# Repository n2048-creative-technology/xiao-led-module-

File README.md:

# XIAO LED Module

A 44 x 21 mm addressable-LED panel built around a **Seeed Studio XIAO
ESP32-C3**, driving **50 WS2812B-compatible RGB LEDs** (2020 package)
arranged as two 25-LED daisy chains, plus a 4-pin JST-PH connector for
external power/data breakout.

## 3D Renders

| Top side (LED array) | Bottom side (XIAO socket) |
|---|---|
|  |  |

## Schematic

Full-resolution vector version: [`docs/images/schematic.pdf`](docs/images/schematic.pdf)

## PCB Layout

*Copper (F.Cu / B.Cu), silkscreen, and solder mask layers, board outline shown.*

## Board Specs

- **Size:** 44.05 mm x 21.05 mm
- **Layers:** 2 (F.Cu / B.Cu)
- **MCU:** Seeed Studio XIAO ESP32-C3 (socketed, not soldered — see Manufacturing below)
- **LEDs:** 50x WS2812B-compatible addressable RGB LED, 2020 package,
  arranged as two independent 25-LED daisy chains (LEDA / LEDB) driven
  from separate GPIO pins
- **Power/data breakout:** J2, 4-pin JST-PH 2.0mm right-angle SMD connector
- **Power in:** +5V rail feeds the LED array; XIAO module handles its
  own onboard 3.3V regulation

## Bill of Materials

All parts verified against the live JLCPCB Open Platform API (real-time stock/pricing).

| Ref | Part | LCSC # | Library | Qty |
|---|---|---|---|---|
| D1-D50 | XL-2020RGBC-2812B (WS2812B-compatible RGB LED) | C5349955 | Extended | 50 |
| J2 | WAFER-PH2.0-4PWB (JST-PH-compatible 4-pin SMD connector) | C3029442 | Extended | 1 |
| U1 | Seeed XIAO ESP32-C3 | — | **Not JLCPCB-assembled, see below** | 1 |

### Part substitution notes

- **D1-D50 (LEDs):** the schematic's original part, WS2812B-2020
  (LCSC C965555), has only **4 units** in live JLCPCB stock — unusable
  for a 50-LED board. Replaced with **XL-2020RGBC-2812B (C5349955,
  127,770 in stock)** — confirmed via XINGLIGHT's datasheet to share
  the same 2.0x2.0mm package, the same VDD/GND/DI/DO pin-out, and
  WS2812 protocol compatibility. Direct drop-in on the existing
  `WS2812_2020` footprint.
- **J2 (connector):** the original part, JST S4B-PH-SM4-GW-TB
  (LCSC C265331), shows **0 units** in stock. Replaced with
  **WAFER-PH2.0-4PWB (C3029442, 45,426 in stock)** — same 4-pin,
  2.0mm-pitch, right-angle SMD JST-PH-compatible connector family,
  confirmed on the existing `JST_1x04_P2.0mm_Horizontal_SMD` footprint.
- **U1 (XIAO module):** the board footprint (`XIAO-ESP32-C3-DIP`) is a
  **socket pattern** — 14 pads in 2 rows at 2.54mm pitch, each with
  both a through-hole and an SMD land, designed so a plug-in XIAO
  module can be inserted rather than reflow-soldered. JLCPCB does not
  stock a machine-placeable 2.54mm female pin socket (a known
  limitation for tall THT sockets on their SMT assembly line), so **U1
  is marked DNP (Do Not Populate)** in the BOM/CPL. The board still
  gets the correct through-holes drilled; **hand-solder a standard
  1x7, 2.54mm female header pair into the U1 pads after fabrication**,
  then plug in your XIAO ESP32-C3.

## Manufacturing

`production/` contains regenerated, verified fabrication files:

- `xiao_led_module_gerbers.zip` — Gerbers + Excellon drill file
  (upload directly to JLCPCB's PCB order)
- `bom.csv` — JLCPCB-format BOM (Comment/Designator/Footprint/LCSC
  Part #) covering the 51 machine-assembled parts (50 LEDs + J2).
  **U1 is intentionally excluded** — see part substitution notes above.
- `positions.csv` — CPL / pick-and-place file, generated with
  `--exclude-dnp` so U1 is correctly omitted from placement while
  everything else retains accurate position/rotation/side data

### 3D view in KiCad

- **D1-D50 (LEDs):** the `WS2812_2020` footprint carries a real,
  present STEP model — renders correctly out of the box.
- **J2 (connector):** the SMD JST-PH "SM4" footprint family has **no
  3D model anywhere**, including KiCad's own upstream
  `kicad-packages3D` repo — a known gap in the official library, not
  something fixable from this repo. A through-hole JST-PH variant
  (`S4B-PH-K`, LCSC C157926, 18,711 in stock) *does* have a working
  model, but switching to it means a mechanical footprint change
  (SMD → THT); left as SMD per current board design.
- **U1 (XIAO module):** the footprint's bundled 3D models point at
  `${AMZPATH}`, a third-party model pack (from whoever originally
  authored this footprint) that isn't publicly distributed anywhere
  findable. Seeed's own official OPL KiCad library ships the
  *identical* footprint with the same broken reference. JLCPCB-side
  alternatives (direct XIAO ESP32-C3 module SKUs C19189385 and
  C18212168) are both essentially out of stock (0 and 1 units,
  respectively) regardless, so U1 was staying DNP either way — the
  missing 3D preview here is cosmetic only.

### Design Rule Check status

`kicad-cli pcb drc` reports 12 violations (4 starved-thermal errors on
zone-connected pads, plus silkscreen/track warnings) — all confirmed
**pre-existing** in the original committed board, unrelated to this
sourcing pass (verified via `git stash` diff-check: identical
violation set before and after the BOM/CPL changes). No new errors
introduced by the part substitutions.

## Repo Layout

```
xiao led module.kicad_pro   KiCad project
xiao led module.kicad_sch   Schematic
xiao led module.kicad_pcb   PCB layout
docs/images/                 Renders and diagrams (this README)
production/                   JLCPCB-ready fabrication output:
  xiao_led_module_gerbers.zip    Gerbers + drill (upload as-is)
  bom.csv                        JLCPCB BOM (50 LEDs + J2; U1 excluded, DNP)
  positions.csv                  CPL / pick-and-place file (DNP-excluded)
  gerbers/                       Individual Gerber/drill layer files
```

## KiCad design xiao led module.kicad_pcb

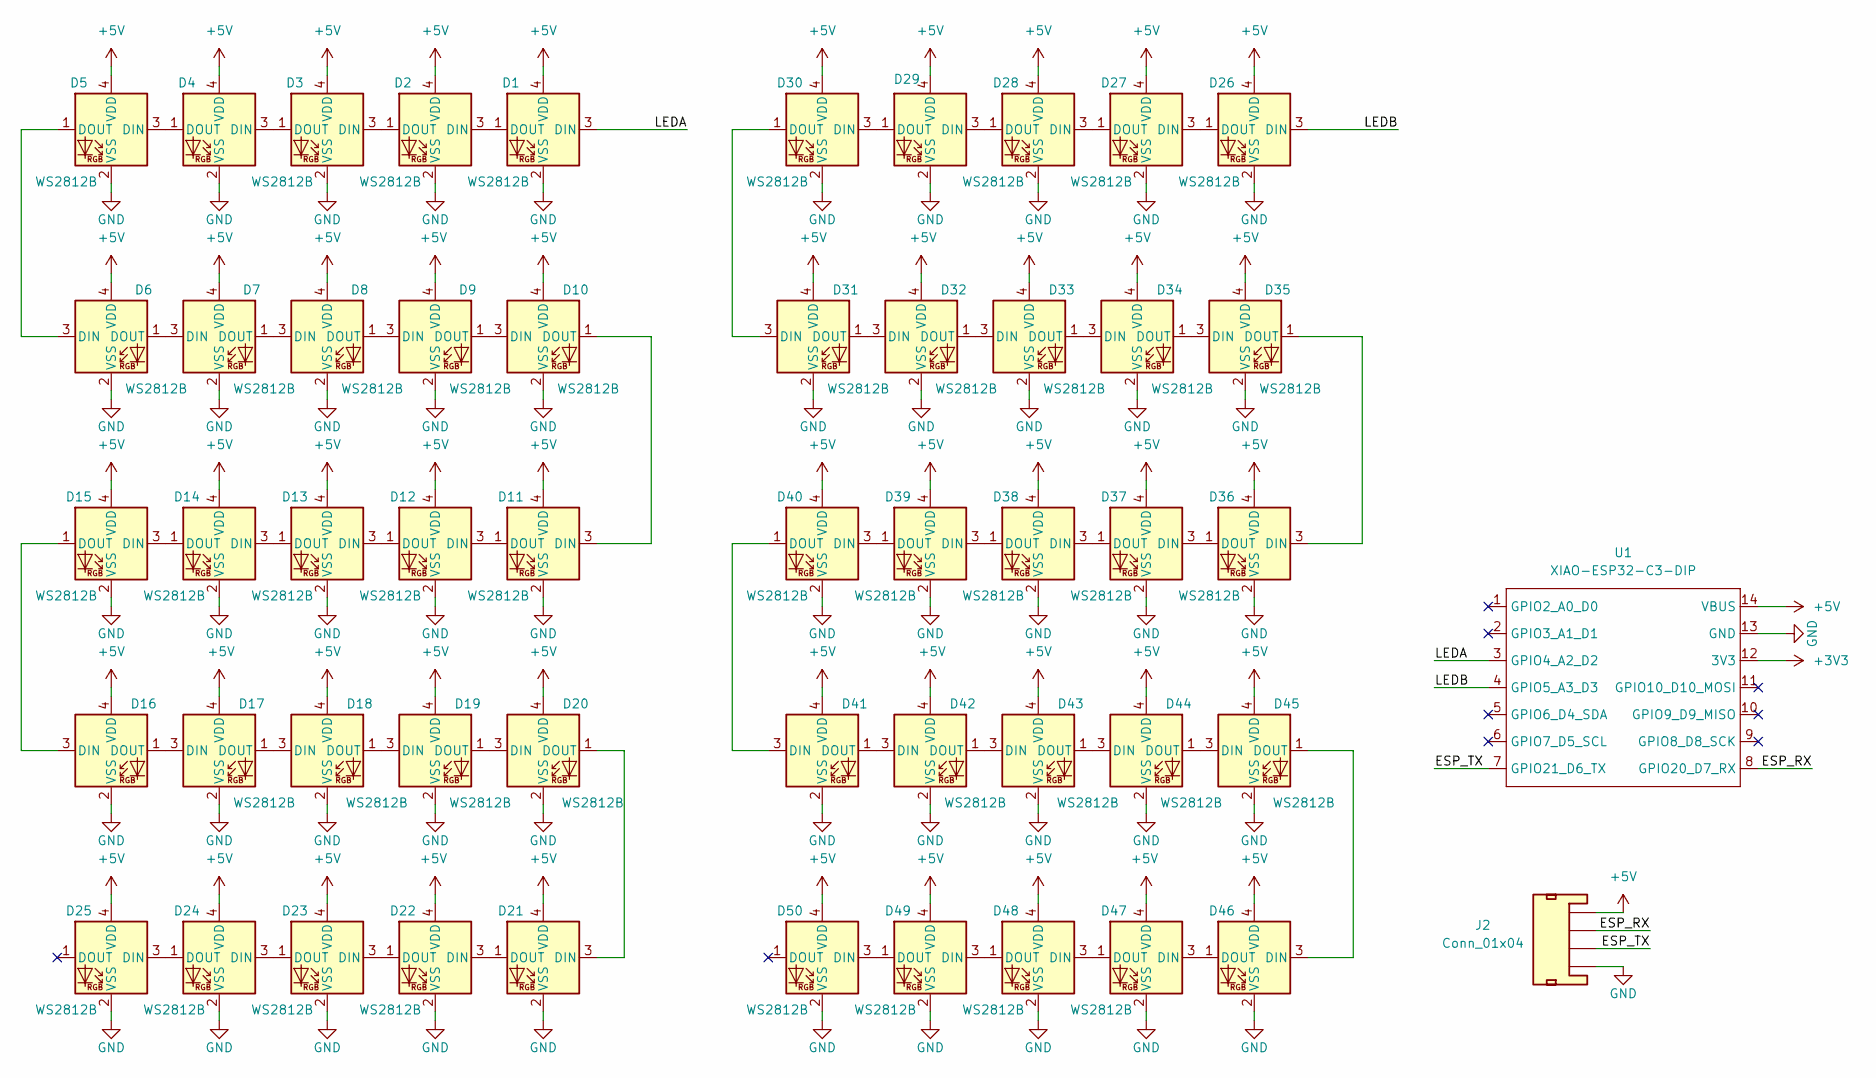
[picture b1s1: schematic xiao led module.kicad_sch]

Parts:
D1, D2, D3, D4, D5, D6, D7, D8, D9, D10, D11, D12, D13, D14, D15, D16, D17, D18, D19, D20, D21, D22, D23, D24, D25, D26, D27, D28, D29, D30, D31, D32, D33, D34, D35, D36, D37, D38, D39, D40, D41, D42, D43, D44, D45, D46, D47, D48, D49, D50: WS2812B; WS2812_2020; MPN XL-2020RGBC-2812B; LCSC C5349955
J2: Conn_01x04; JST_1x04_P2.0mm_Horizontal_SMD; MPN WAFER-PH2.0-4PWB; LCSC C3029442
U1: XIAO-ESP32-C3-DIP; MPN DNP - hand-solder 2x 1x7 2.54mm female 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

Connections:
+3V3: U1.12 (3V3)
+5V: D1.4 (VDD), D2.4 (VDD), D3.4 (VDD), D4.4 (VDD), D5.4 (VDD), D6.4 (VDD), D7.4 (VDD), D8.4 (VDD), D9.4 (VDD), D10.4 (VDD), D11.4 (VDD), D12.4 (VDD), D13.4 (VDD), D14.4 (VDD), D15.4 (VDD), D16.4 (VDD), D17.4 (VDD), D18.4 (VDD), D19.4 (VDD), D20.4 (VDD), D21.4 (VDD), D22.4 (VDD), D23.4 (VDD), D24.4 (VDD), D25.4 (VDD), D26.4 (VDD), D27.4 (VDD), D28.4 (VDD), D29.4 (VDD), D30.4 (VDD), D31.4 (VDD), D32.4 (VDD), D33.4 (VDD), D34.4 (VDD), D35.4 (VDD), D36.4 (VDD), D37.4 (VDD), D38.4 (VDD), D39.4 (VDD), D40.4 (VDD), D41.4 (VDD), D42.4 (VDD), D43.4 (VDD), D44.4 (VDD), D45.4 (VDD), D46.4 (VDD), D47.4 (VDD), D48.4 (VDD), D49.4 (VDD), D50.4 (VDD), J2.1, U1.14 (VBUS)
/ESP_RX: J2.2, U1.8 (GPIO20_D7_RX)
/ESP_TX: J2.3, U1.7 (GPIO21_D6_TX)
/LEDA: D1.3 (DIN), U1.3 (GPIO4_A2_D2)
/LEDB: D26.3 (DIN), U1.4 (GPIO5_A3_D3)
GND: D1.2 (VSS), D2.2 (VSS), D3.2 (VSS), D4.2 (VSS), D5.2 (VSS), D6.2 (VSS), D7.2 (VSS), D8.2 (VSS), D9.2 (VSS), D10.2 (VSS), D11.2 (VSS), D12.2 (VSS), D13.2 (VSS), D14.2 (VSS), D15.2 (VSS), D16.2 (VSS), D17.2 (VSS), D18.2 (VSS), D19.2 (VSS), D20.2 (VSS), D21.2 (VSS), D22.2 (VSS), D23.2 (VSS), D24.2 (VSS), D25.2 (VSS), D26.2 (VSS), D27.2 (VSS), D28.2 (VSS), D29.2 (VSS), D30.2 (VSS), D31.2 (VSS), D32.2 (VSS), D33.2 (VSS), D34.2 (VSS), D35.2 (VSS), D36.2 (VSS), D37.2 (VSS), D38.2 (VSS), D39.2 (VSS), D40.2 (VSS), D41.2 (VSS), D42.2 (VSS), D43.2 (VSS), D44.2 (VSS), D45.2 (VSS), D46.2 (VSS), D47.2 (VSS), D48.2 (VSS), D49.2 (VSS), D50.2 (VSS), J2.4, J2.NC1, J2.NC2, U1.13 (GND)
unnamed: D1.1 (DOUT), D2.3 (DIN)
unnamed: D2.1 (DOUT), D3.3 (DIN)
unnamed: D3.1 (DOUT), D4.3 (DIN)
unnamed: D4.1 (DOUT), D5.3 (DIN)
unnamed: D5.1 (DOUT), D6.3 (DIN)
unnamed: D6.1 (DOUT), D7.3 (DIN)
unnamed: D7.1 (DOUT), D8.3 (DIN)
unnamed: D8.1 (DOUT), D9.3 (DIN)
unnamed: D9.1 (DOUT), D10.3 (DIN)
unnamed: D10.1 (DOUT), D11.3 (DIN)
unnamed: D11.1 (DOUT), D12.3 (DIN)
unnamed: D12.1 (DOUT), D13.3 (DIN)
unnamed: D13.1 (DOUT), D14.3 (DIN)
unnamed: D14.1 (DOUT), D15.3 (DIN)
unnamed: D15.1 (DOUT), D16.3 (DIN)
unnamed: D16.1 (DOUT), D17.3 (DIN)
unnamed: D17.1 (DOUT), D18.3 (DIN)
unnamed: D18.1 (DOUT), D19.3 (DIN)
unnamed: D19.1 (DOUT), D20.3 (DIN)
unnamed: D20.1 (DOUT), D21.3 (DIN)
unnamed: D21.1 (DOUT), D22.3 (DIN)
unnamed: D22.1 (DOUT), D23.3 (DIN)
unnamed: D23.1 (DOUT), D24.3 (DIN)
unnamed: D24.1 (DOUT), D25.3 (DIN)
unnamed: D26.1 (DOUT), D27.3 (DIN)
unnamed: D27.1 (DOUT), D28.3 (DIN)
unnamed: D28.1 (DOUT), D29.3 (DIN)
unnamed: D29.1 (DOUT), D30.3 (DIN)
unnamed: D30.1 (DOUT), D31.3 (DIN)
unnamed: D31.1 (DOUT), D32.3 (DIN)
unnamed: D32.1 (DOUT), D33.3 (DIN)
unnamed: D33.1 (DOUT), D34.3 (DIN)
unnamed: D34.1 (DOUT), D35.3 (DIN)
unnamed: D35.1 (DOUT), D36.3 (DIN)
unnamed: D36.1 (DOUT), D37.3 (DIN)
unnamed: D37.1 (DOUT), D38.3 (DIN)
unnamed: D38.1 (DOUT), D39.3 (DIN)
unnamed: D39.1 (DOUT), D40.3 (DIN)
unnamed: D40.1 (DOUT), D41.3 (DIN)
unnamed: D41.1 (DOUT), D42.3 (DIN)
unnamed: D42.1 (DOUT), D43.3 (DIN)
unnamed: D43.1 (DOUT), D44.3 (DIN)
unnamed: D44.1 (DOUT), D45.3 (DIN)
unnamed: D45.1 (DOUT), D46.3 (DIN)
unnamed: D46.1 (DOUT), D47.3 (DIN)
unnamed: D47.1 (DOUT), D48.3 (DIN)
unnamed: D48.1 (DOUT), D49.3 (DIN)
unnamed: D49.1 (DOUT), D50.3 (DIN)

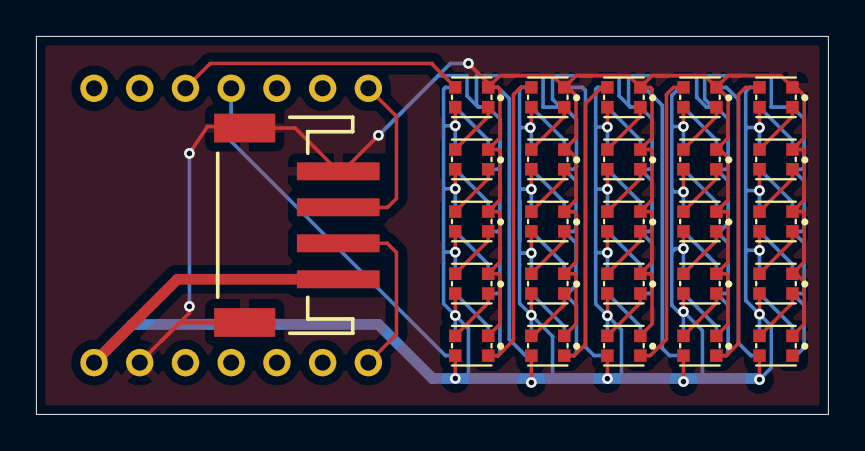
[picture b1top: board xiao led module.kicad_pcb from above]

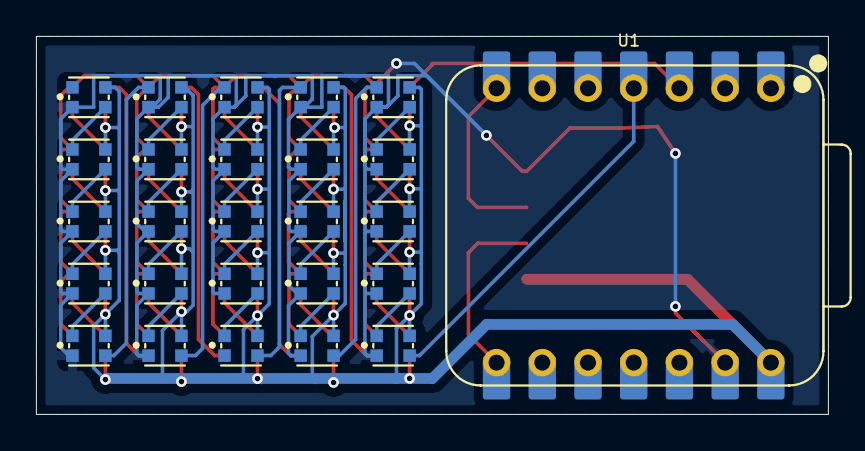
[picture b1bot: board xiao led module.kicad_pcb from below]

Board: 2 copper layers, 44.0 x 21.0 mm, 52 parts (26 on the bottom side), 54 nets.

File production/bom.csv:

Comment,Designator,Footprint,LCSC Part #
WS2812B,"D1,D2,D3,D4,D5,D6,D7,D8,D9,D10,D11,D12,D13,D14,D15,D16,D17,D18,D19,D20,D21,D22,D23,D24,D25,D26,D27,D28,D29,D30,D31,D32,D33,D34,D35,D36,D37,D38,D39,D40,D41,D42,D43,D44,D45,D46,D47,D48,D49,D50",WS2812_2020,C5349955
Conn_01x04,J2,JST_1x04_P2.0mm_Horizontal_SMD,C3029442
